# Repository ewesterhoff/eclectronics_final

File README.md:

# Eclectronics Final Project

We're building a mini rover that will find tennis balls using bluetooth tracking

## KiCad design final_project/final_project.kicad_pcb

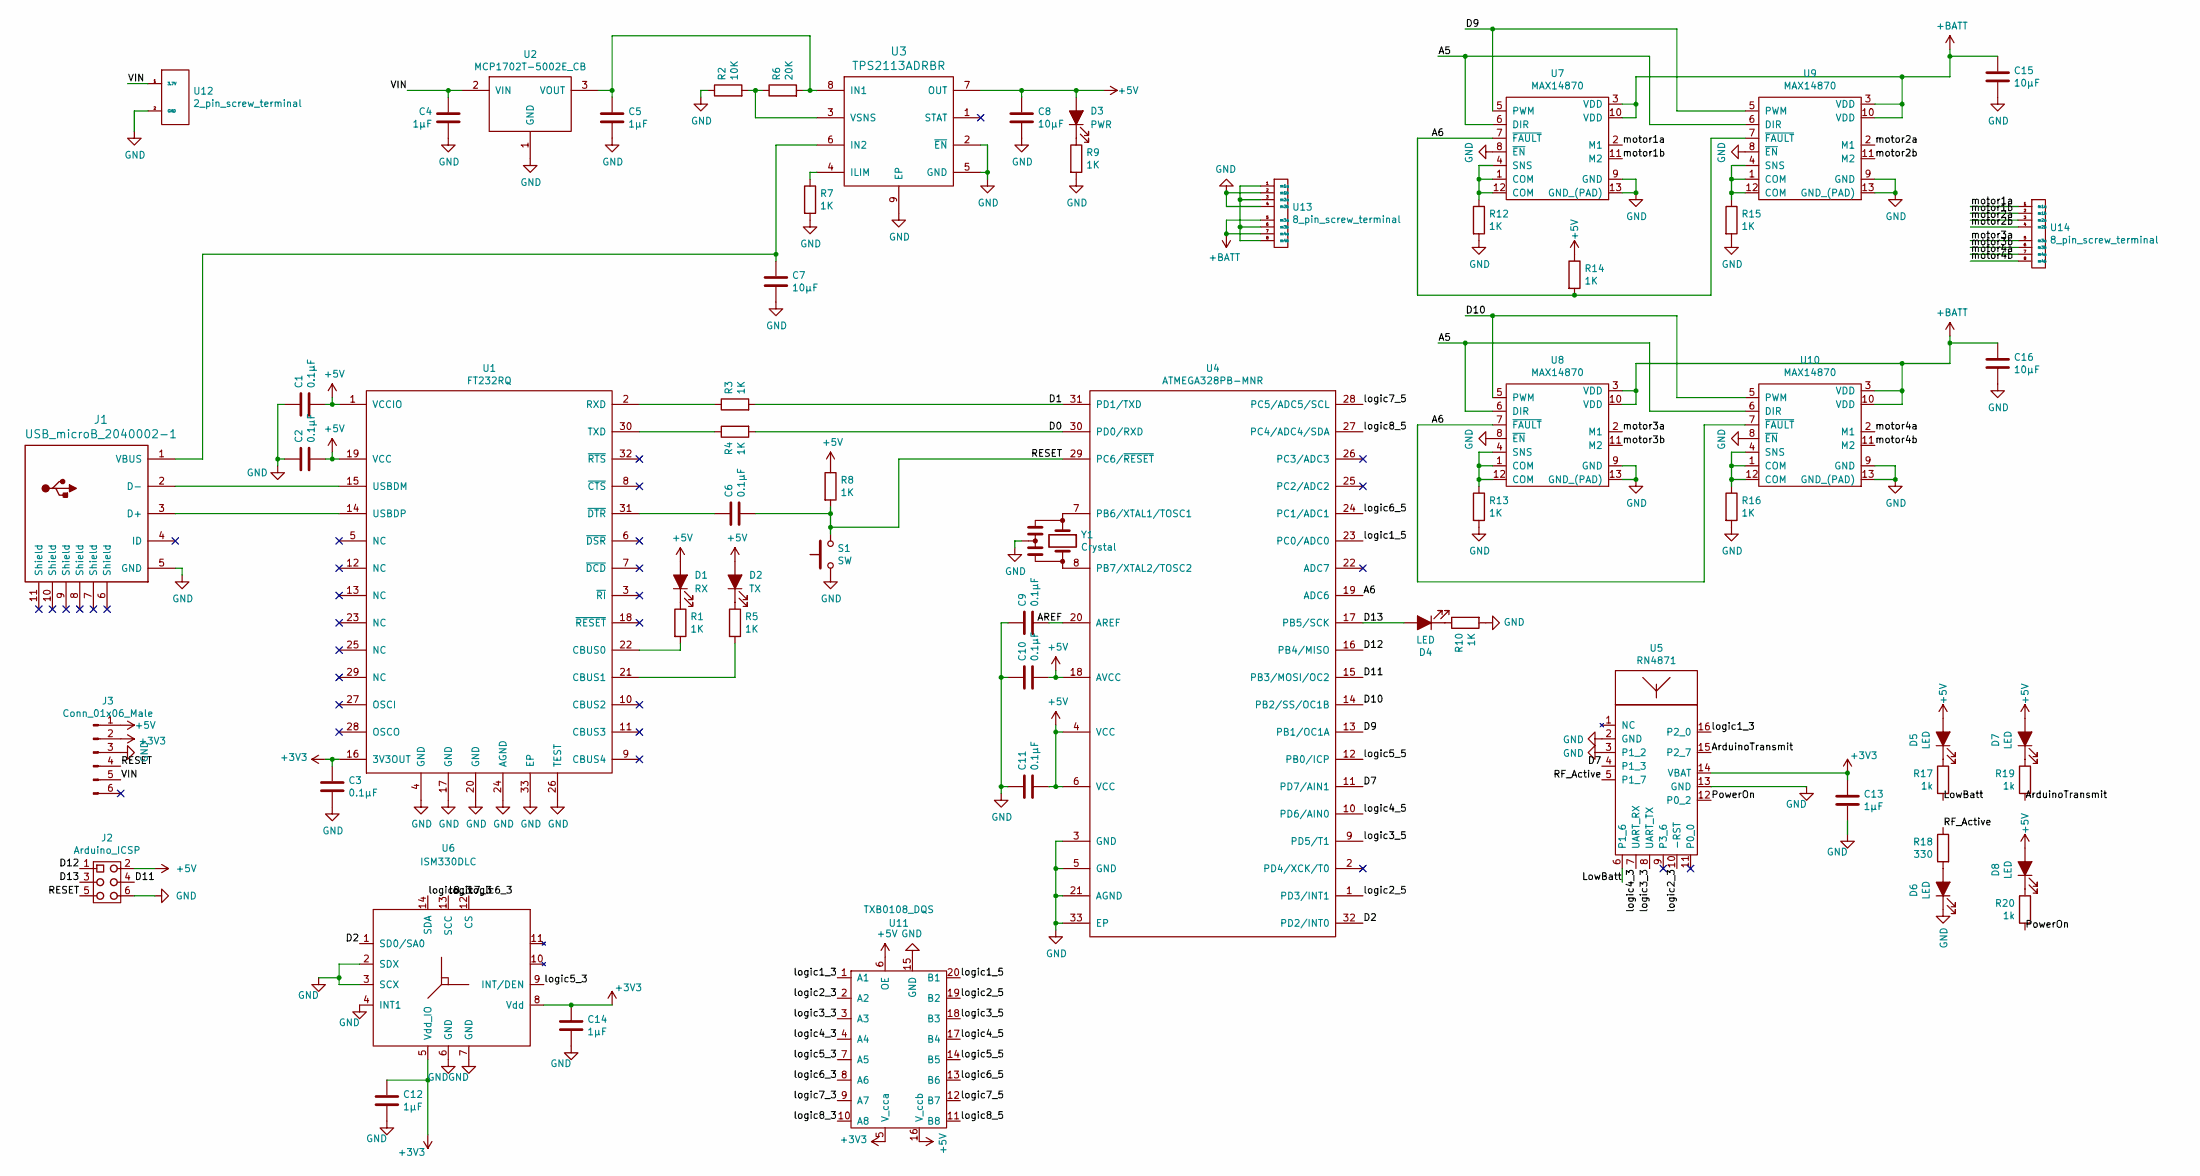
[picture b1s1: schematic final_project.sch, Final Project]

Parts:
C1, C2, C3, C6, C9, C10, C11: 0.1µF; C_0603_1608Metric
C4, C5, C12, C13, C14: 1µF; C_0603_1608Metric
C7, C8, C15, C16: 10µF; C_0805_2012Metric
D1: RX; LED_0805_2012Metric
D2: TX; LED_0805_2012Metric
D3: PWR; LED_0805_2012Metric
D4, D5, D6, D7, D8: LED; LED_0805_2012Metric
J1: USB_microB_2040002-1
J2: Arduino_ICSP
J3: Conn_01x06_Male; PinHeader_1x06_P2.54mm_Vertical
R1, R3, R4, R5, R7, R8, R9, R10, R12, R13, R14, R15, R16: 1K; R_0603_1608Metric
R2: 10K; R_0603_1608Metric
R6: 20K; R_0603_1608Metric
R17, R19, R20: 1k; R_0603_1608Metric
R18: 330; R_0603_1608Metric
S1: SW; SW_SPST_B3U-1000P
U1: FT232RQ
U2: MCP1702T-5002E_CB; SOT-23
U3: TPS2113ADRBR; TSP2113A-DRBR
U4: ATMEGA328PB-MNR; ATmega328
U5: RN4871
U6: ISM330DLC
U7, U8, U9, U10: MAX14870; TDFN-12-1EP_3x3
U11: TXB0108_DQS; USON-20_2x4mm_P0.4mm
U12: 2_pin_screw_terminal; 2_pin_screw
U13, U14: 8_pin_screw_terminal; 8_pin_screw
Y1: Crystal; CSTNE

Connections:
+BATT: C15.1, C16.1, U7.3 (VDD), U7.10 (VDD), U8.3 (VDD), U8.10 (VDD), U9.3 (VDD), U9.10 (VDD), U10.3 (VDD), U10.10 (VDD), U13.5 (m3a), U13.7 (m4a)
/A5: U7.6 (DIR), U8.6 (DIR), U9.6 (DIR), U10.6 (DIR)
/A6: R14.2, U4.19 (ADC6), U7.7 (~FAULT), U8.7 (~FAULT), U9.7 (~FAULT), U10.7 (~FAULT)
/AREF: C9.2, U4.20 (AREF)
/ArduinoTransmit: R19.2, U5.15 (P2_7)
/D0: R4.2, U4.30 (PD0/RXD)
/D1: R3.2, U4.31 (PD1/TXD)
/D2: U4.32 (PD2/INT0), U6.1 (SD0/SA0)
/D7: U4.11 (PD7/AIN1), U5.4 (P1_3)
/D9: U4.13 (PB1/OC1A), U7.5 (PWM), U9.5 (PWM)
/D10: U4.14 (PB2/SS/OC1B), U8.5 (PWM), U10.5 (PWM)
/D11: J2.4, U4.15 (PB3/MOSI/OC2)
/D12: J2.1, U4.16 (PB4/MISO)
/D13: D4.2 (A), J2.3, U4.17 (PB5/SCK)
/LowBatt: R17.2, U5.6 (P1_6)
/PowerOn: R20.2, U5.12 (P0_2)
/RESET: C6.2, J2.5, J3.4, R8.2, S1.2, U4.29 (PC6/~RESET)
/RF_Active: R18.1, U5.5 (P1_7)
/VIN: C4.1, J3.5, U2.2 (VIN), U12.1 (3.7V)
/logic1_3: U5.16 (P2_0), U11.1 (A1)
/logic1_5: U4.23 (PC0/ADC0), U11.20 (B1)
/logic2_3: U5.10 (-RST), U11.2 (A2)
/logic2_5: U4.1 (PD3/INT1), U11.19 (B2)
/logic3_3: U5.8 (UART_TX), U11.3 (A3)
/logic3_5: U4.9 (PD5/T1), U11.18 (B3)
/logic4_3: U5.7 (UART_RX), U11.4 (A4)
/logic4_5: U4.10 (PD6/AIN0), U11.17 (B4)
/logic5_3: U6.9 (INT/DEN), U11.7 (A5)
/logic5_5: U4.12 (PB0/ICP), U11.14 (B5)
/logic6_3: U6.12 (CS), U11.8 (A6)
/logic6_5: U4.24 (PC1/ADC1), U11.13 (B6)
/logic7_3: U6.13 (SCC), U11.9 (A7)
/logic7_5: U4.28 (PC5/ADC5/SCL), U11.12 (B7)
/logic8_3: U6.14 (SDA), U11.10 (A8)
/logic8_5: U4.27 (PC4/ADC4/SDA), U11.11 (B8)
/motor1a: U7.2 (M1), U14.1 (m1a)
/motor1b: U7.11 (M2), U14.2 (m1b)
/motor2a: U9.2 (M1), U14.3 (m2a)
/motor2b: U9.11 (M2), U14.4 (m2b)
/motor3a: U8.2 (M1), U14.5 (m3a)
/motor3b: U8.11 (M2), U14.6 (m3b)
/motor4a: U10.2 (M1), U14.7 (m4a)
/motor4b: U10.11 (M2), U14.8 (m4b)
GND: C1.1, C2.1, C3.2, C4.2, C5.2, C7.2, C8.2, C9.1, C10.1, C11.1, C12.2, C13.2, C14.2, C15.2, C16.2, D6.1 (K), J1.5 (GND), J2.6, J3.3, R2.1, R7.2, R9.2, R10.2, R12.2, R13.2, R15.2, R16.2, S1.1, U1.4 (GND), U1.17 (GND), U1.20 (GND), U1.24 (AGND), U1.26 (TEST), U1.33 (EP), U2.1 (GND), U3.2 (~EN), U3.5 (GND), U3.9 (EP), U4.3 (GND), U4.5 (GND), U4.21 (AGND), U4.33 (EP), U5.2 (GND), U5.3 (P1_2), U5.13 (GND), U6.2 (SDX), U6.3 (SCX), U6.4 (INT1), U6.6 (GND), U6.7 (GND), U7.8 (~EN), U7.9 (GND), U7.13 (GND_(PAD)), U8.8 (~EN), U8.9 (GND), U8.13 (GND_(PAD)), U9.8 (~EN), U9.9 (GND), U9.13 (GND_(PAD)), U10.8 (~EN), U10.9 (GND), U10.13 (GND_(PAD)), U11.15 (GND), U12.2 (GND), U13.2 (m1b), U13.4 (m2b), Y1.2
unnamed: C5.1, R6.2, U2.3 (VOUT), U3.8 (IN1)
unnamed: C6.1, U1.31 (~DTR)
unnamed: C7.1, J1.1 (VBUS), U3.6 (IN2)
unnamed: D1.1 (K), R1.1
unnamed: D2.1 (K), R5.1
unnamed: D3.1 (K), R9.1
unnamed: D4.1 (K), R10.1
unnamed: D5.1 (K), R17.1
unnamed: D6.2 (A), R18.2
unnamed: D7.1 (K), R19.1
unnamed: D8.1 (K), R20.1
unnamed: J1.2 (D-), U1.15 (USBDM)
unnamed: J1.3 (D+), U1.14 (USBDP)
unnamed: R1.2, U1.22 (CBUS0)
unnamed: R2.2, R6.1, U3.3 (VSNS)
unnamed: R3.1, U1.2 (RXD)
unnamed: R4.1, U1.30 (TXD)
unnamed: R5.2, U1.21 (CBUS1)
unnamed: R7.1, U3.4 (ILIM)
unnamed: R12.1, U7.1 (COM), U7.4 (SNS), U7.12 (COM)
unnamed: R13.1, U8.1 (COM), U8.4 (SNS), U8.12 (COM)
unnamed: R15.1, U9.1 (COM), U9.4 (SNS), U9.12 (COM)
unnamed: R16.1, U10.1 (COM), U10.4 (SNS), U10.12 (COM)
unnamed: U4.7 (PB6/XTAL1/TOSC1), Y1.1
unnamed: U4.8 (PB7/XTAL2/TOSC2), Y1.3
unnamed: U13.1 (m1a), U13.3 (m2a), U13.6 (m3b), U13.8 (m4b)

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
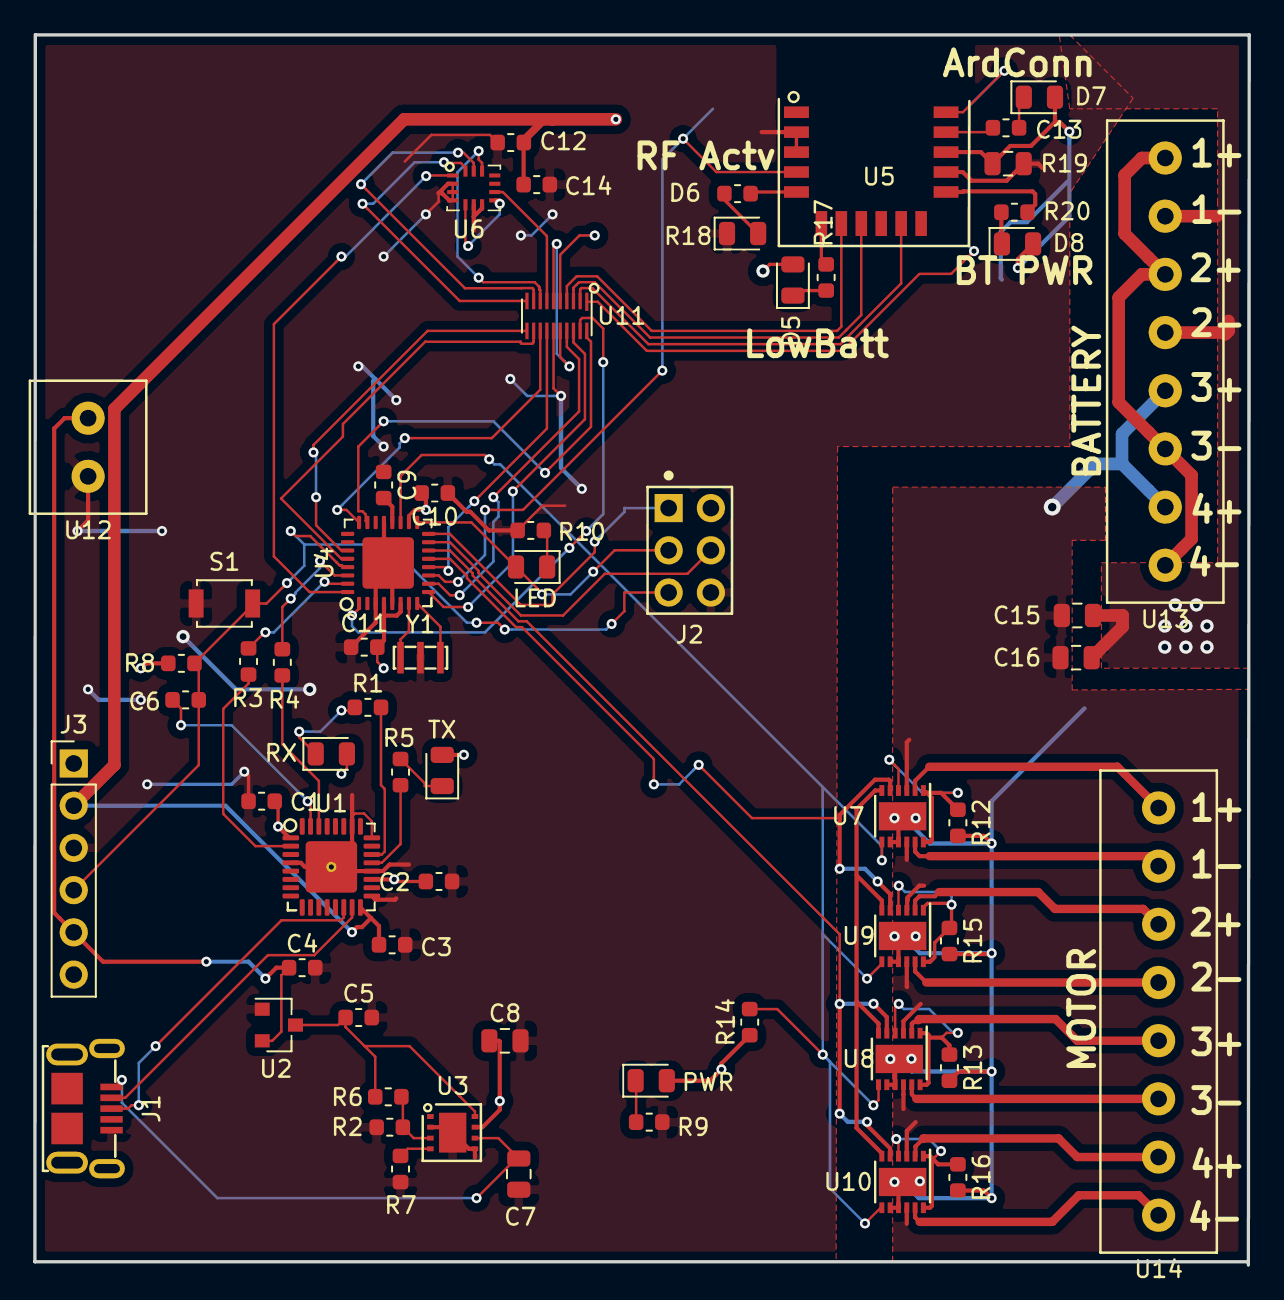
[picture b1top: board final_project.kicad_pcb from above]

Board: 2 copper layers, 73.0 x 74.0 mm, 62 parts (0 on the bottom side), 72 nets.

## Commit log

2019-04-02 initial footprint association
2019-04-02 Create mp3b.lib
    Added library hopefully
2019-04-04 full footprints
2019-04-04 add rn symbol
2019-04-04 rn4871 application circuit
2019-04-04 add tx LED
2019-04-05 update schematic
2019-04-06 IMU and Bluetooth footprints
2019-04-06 symbol for MAX14870
2019-04-07 new schmeatic
2019-04-08 add logic level converter
2019-04-09 adding power and motor connectors (symbols and footprints)
2019-04-10 new things
2019-04-10 adding footprint for motor controllers and attatching some other footprints
2019-04-10 TDFN's
2019-04-10 first pass layout
2019-04-11 updated layout v1
2019-04-13 layout update
2019-04-15 layout edit ground traces
2019-05-04 BT Arduino code
    Some code
2019-05-06 Create BTCode.ino
    now with hex conversion and all of that jazz
2019-05-06 cleaned up github
    also motors integrated into BTCode
2019-05-06 Update BTCode.ino
    now with taking the derivative over time
2019-05-07 wheel test code and BTCode changes
    -BTCode now goes backwards/forwards (direction-based changes rather than turning)
    -code used to test wheels now on github
2019-05-07 buffer smaller now
    Other details:
    -more comments
    -LED now indicating direction
    -pwm pins initialized to 0
    -2 Hz cycle
    -pwmStrength range increase
2019-05-07 Update BTCode.ino
    take out extra print lines
